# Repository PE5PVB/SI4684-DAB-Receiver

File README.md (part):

# SI4684 FM/DAB Receiver v2.2.1

Advanced FM, RDS/RBDS, DAB/DAB+ and DAB SlideShow receiver for the **Skyworks SI4684**, **ESP32-WROOM-32D** and a **320×240 ILI9341** display.

Firmware v2.2.1 uses separate SPI controllers for the TFT and radio, supports learned IR remote control, FM/DAB presets, multilingual UI, DAB MOT SlideShow, light-sleep standby and an optional serial control/diagnostic interface. It includes a project-local universal **Si468x driver library** that centralizes the tuner command/CTS/error state machine and supports both bounded polling and real **INTB interrupt-driven handling**.

This project is based on the original open-source SI4684/DAB receiver work published by **PE5PVB**.

## Complete ESP32 build image

Every successful `pio run -e esp32dev` also creates
`.pio/build/esp32dev/receiver-complete.bin`, containing the bootloader,
partition table, boot application image and receiver firmware. Flash this
combined file at **0x0**. Its blank padding covers the NVS partition, so
flashing it clears saved settings, presets and station lists. For normal
updates that retain NVS, use `pio run -e esp32dev -t upload` instead.

The same build also generates `.pio/build/esp32dev/flash-addresses.txt` with
the flash addresses and filenames for the combined image and each individual image.
The framework-provided `boot_app0.bin` is copied into the same build directory,
so all listed binary files are available together.
Choose either the combined image or the individual images when flashing.

> [!CAUTION]
> ## GPIO12 / MTDI eFuse requirement — read before using INTB or IR
>
> On the classic ESP32, **GPIO12 is also the MTDI boot-strapping pin**. At reset it normally selects the VDD_SDIO flash voltage:
>
> - GPIO12 LOW or unconnected → **3.3 V**
> - GPIO12 HIGH → **1.8 V**
>
> **ESP32-WROOM-32D uses 3.3 V flash. For this project, program the VDD_SDIO eFuses to a fixed 3.3 V before using GPIO12 as either Si4684 INTB or IR receiver input.** This also applies to `GPIO12 = AUTO` if the INTB line is physically fitted.
>
> An Si4684 INTB output or a demodulated IR receiver normally idles HIGH. Without the eFuse override, a HIGH level present during reset can select 1.8 V for a 3.3 V flash device and the ESP32 may fail to boot.
>
> If GPIO12 is physically unconnected and the radio is used in polling mode, the eFuse change is not required. A hardware design that independently guarantees the correct VDD_SDIO voltage/strap can also solve the problem, but the standard WROOM-32D build in this project should treat the 3.3 V eFuse setting as mandatory for INTB or IR.
>
> **eFuse programming is permanent and cannot be undone. Verify that the ESP32 module really uses 3.3 V flash before burning it. Do not burn 3.3 V on a module that requires 1.8 V flash.**

Official Espressif references:

- [Set Flash Voltage — ESP32 / espefuse](https://docs.espressif.com/projects/esptool/en/latest/esp32/espefuse/set-flash-voltage-cmd.html)
- [Espressif FAQ — using GPIO12 on ESP32-WROOM-32D](https://docs.espressif.com/projects/esp-faq/en/latest/hardware-related/hardware-design.html)

---

## Main features

### DAB / DAB+

- DAB and DAB+ reception with SI4684.
- Uses the **Skyworks proprietary Si4684 DAB application firmware image** loaded into the tuner at runtime (`dab_6_0_9`, firmware 6.0.9 in the current build).
- Manual multiplex selection, automatic seek/scan and memory mode.
- Up to **99 DAB presets**.
- Ensemble and service list handling.
- Service selection from the channel/service list.
- Service ID (SID), Ensemble ID (EID), ECC/country information.
- Programme Type (PTY).
- Dynamic Label / DLS radiotext.
- Bitrate, sample rate, audio mode, service type and protection information when supplied by the tuner.
- DAB time/date information.
- DAB SlideShow / MOT reception.
- Automatic or manual SlideShow display.
- Character conversion for DAB labels/DLS including EBU Latin, UCS-2 and UTF-8 paths used by the firmware.

### FM

- FM reception using the **Skyworks proprietary Si4684 FM/FMHD application firmware image** loaded into the tuner at runtime (`fmhd_5_3_3`, firmware 5.3.3 in the current build).
- FM reception with regional band profiles:
  - **Europe:** 87.5–108.0 MHz, 100 kHz raster, 50 µs de-emphasis, RDS.
  - **North America:** 87.9–107.9 MHz, 200 kHz raster, 75 µs de-emphasis, RBDS.
  - **Japan:** 76.0–95.0 MHz, 100 kHz raster, 50 µs de-emphasis, RDS.
- Manual tuning, automatic seek and memory mode.
- Up to **99 FM presets**.
- RDS/RBDS:
  - PI, region-specific PTY text, PS and RadioText;
  - AF list decoding from group 0A plus optional, default-off automatic AF
    switching with mandatory PI verification and RSSI/SNR hysteresis;
  - TP and TA indicators;
  - validated group 4A Clock-Time/date, shown in System Information and used
    for the displayed local clock after applying the broadcast UTC offset;
  - bounded full-band station scan with PI/PS/RSSI/SNR list records;
  - stabilized PS and RadioText assembly.
- Stereo/mono indication.
- Stereo blend indication.
- Multipath indication.
- RSSI and SNR display.
- Region-aware fine tuning and seek spacing.

### User interface

- 320×240 ILI9341 color TFT.
- Smooth fonts and sprite-based UI.
- Multiple color themes.
- Adjustable backlight.
- Signal units: `dBµV`, `dBf`, `dBm`.
- Service/channel list.
- System Information screen.
- Configurable inactivity time-out.
- Eight UI languages:
  - English
  - Dutch
  - Greek
  - German
  - French
  - Spanish
  - Polish
  - Romanian

### Other functions

- Learned IR remote control on GPIO12.
- IR Learn / Clear / Test menu.
- Light-sleep standby with state retained in RAM.
- Wake by physical STANDBY button.
- Optional wake by the learned IR STANDBY command when `GPIO12 = IR`.
- Direct NVS settings, presets, learned IR profile and persistent FM/DAB scan lists.
- Serial control protocol at 115200 baud.
- Runtime `DEBUG` command for detailed FM/DAB/RDS/SLS/SPI/RAM diagnostics.
- Shared ILI9341/SI4684 reset recovery.
- Dedicated TFT VSPI and radio HSPI buses.

---

# Hardware

## ESP32

The project targets a classic **ESP32-WROOM-32D / ESP32 Dev Module**.

## TFT — ILI9341 / TFT_eSPI

| Signal | ESP32 GPIO |
|---|---:|
| SCLK | 18 |
| MISO | 19 |
| MOSI | 23 |
| CS | 5 |
| DC | 4 |
| RESET | 17, shared with SI4684 RSTB |
| Backlight PWM | 2 |

The TFT uses **VSPI/SPI3**. `TFT_RST=-1` is intentional: GPIO17 is controlled by the application because the TFT reset and Si4684 RSTB share the same physical net.

## SI4684

| Signal | ESP32 GPIO |
|---|---:|
| SCLK | 14 |
| MISO | 16 |
| MOSI | 13 |
| CS | 15 |
| RSTB | 17, shared with TFT RESET |
| INTB | 12 when fitted |

The Si4684 uses a dedicated **HSPI/SPI2** instance. The radio SPI bus is initialized once and is not re-created during normal FM/DAB operation.

Firmware v2.2.1 uses a project-local universal **`Si468x` driver layer** (`vendor/si468x/Si468x.*`). It provides the common low-level transport and command state machine for the tuner. In particular it supports:

- normal bounded **polling** for CTS/status completion;
- **INTB interrupt-driven** command/event handling when the Si4684 INTB line is connected;
- polling as a safety/fallback path even when INTB is enabled;
- common command/reply parsing and device-error reporting;
- the same transport architecture for both FM and DAB firmware images.

`AUTO` first observes GPIO12 during real tuner commands. If no usable INTB
transition is proven, an unconnected GPIO12 remains in non-blocking polling
mode. With INTB connected, interrupt completion is the fast path and a bounded
2 ms safety poll remains enabled; occasional `ctsPoll` completions do not by
themselves indicate fallback or a wiring fault. The ISR only records an event;
all SPI work remains in the foreground transport pump.

Application-level radio work is scheduled cooperatively and starts at most one
new Si4684 command per pass. Continuous DSRV/MOT traffic is drained in bounded
bursts of four commands; overdue RF status and then one phase-separated metadata
command receive a turn before draining resumes. Stable intervals are:

- DAB RF status 1000 ms; signal/Q UI 500 ms;
- DAB audio and current-service metadata 10 s, ensemble 30 s, time and current
  subchannel 60 s;
- FM RSQ 500 ms; ACF 1000 ms; signal/multipath UI 250 ms;
- FM RDS remains IRQ-driven with an 80 ms polling fallback.

DAB service changes use one explicit non-blocking switch state machine. It
serializes data STOP, audio STOP, a 200 ms settle interval, the new audio START,
another 200 ms settle after confirmation, and only then resolves and starts the
matching data component. A rapid A -> B -> C selection supersedes older request
IDs; completion of an already submitted command is reconciled with the physical
tuner state before the newest request continues. Metadata callbacks only request
data-component evaluation, so there is a single authority that can issue data
START and no callback-driven command storm.

Si4684 `NOT_AVAILABLE` (`0x03`) is treated as a responsive command rejection and
uses bounded non-blocking backoff. It does not trigger a cold reset. Only repeated
CTS timeouts use the existing bounded transport recovery. If slideshow data cannot
be started, audio remains playing and SLS is retried later; MOT objects received
outside the confirmed current data-service context are discarded. Data association
prefers a component with the active audio SID and accepts the legacy ensemble-wide
fallback only when exactly one eligible component exists. Ensembles that carry
MOT/SLS directly in the confirmed audio service PAD do not require a separate
type-3 data-service START; that context becomes valid after audio confirmation
and its settle interval.

The signal display has two stages: each new RF sample updates the radio filter
once, while the faster UI timer only interpolates toward that filtered target.
The `DEBUG` command uses throttled MOT milestones. `DEBUG SLSV` (or
`DEBUG VERBOSE`) explicitly toggles per-segment tracing; low-priority segment
lines are dropped and counted when the UART TX buffer is full.

The current build loads Skyworks-provided proprietary application images into the Si4684 with `LOAD_INIT` / `HOST_LOAD` / `BOOT` when changing the active radio firmware:

- DAB: `dab_6_0_9`
- FM/FMHD: `fmhd_5_3_3`

These tuner firmware images are **proprietary Skyworks material**, not GPL application source code. Their use and redistribution are subject to the applicable Skyworks terms/licence.

## Controls

| Control | ESP32 GPIO |
|---|---:|
| Upper rotary A | 27 |
| Upper rotary B | 34 |
| Upper rotary push / OK | 25 |
| Lower rotary A | 33 |
| Lower rotary B | 32 |
| Lower rotary push / Volume | 35 |
| MODE | 39 |
| STANDBY | 36 |
| SLIDESHOW | 26 |

GPIO34–39 are input-only pins and have no internal pull resistors; the PCB must provide the required external bias.

## Other hardware

- TPA6130A2 headphone amplifier over I²C.
- GPIO17 is a shared active-low hardware reset for both ILI9341 and SI4684.
- GPIO12 is mutually exclusive in the hardware design: connect it to **Si4684 INTB**, **IR receiver output**, or leave it unused. **Do not tie INTB and an IR receiver output together.**

---

# Mandatory eFuse setup for GPIO12 INTB / IR

## Why this is necessary

GPIO12 is not an ordinary GPIO during ESP32 reset. It is sampled as **MTDI** before the application starts and normally controls the internal VDD_SDIO regulator voltage.

For a normal ESP32-WROOM-32D:

| GPIO12 at reset | Default VDD_SDIO |
|---|---:|
| LOW / NC | 3.3 V |
| HIGH | 1.8 V |

Both of the project use cases below can place a HIGH level on GPIO12 before firmware gets control:

1. **Si4684 INTB connected to GPIO12** — includes explicit `INTB` mode and `AUTO` mode on hardware with INTB fitted.
2. **Demodulated IR receiver connected to GPIO12** — IR receiver outputs normally idle HIGH.

Therefore the recommended and expected configuration for the WROOM-32D build is to permanently force VDD_SDIO to **3.3 V** by eFuse.

## Short programming guide

Install a recent Espressif `esptool` package and identify the ESP32 serial port. The following example uses `COM5`; replace it with your actual port.

### 1. Read the current eFuse state

```text
espefuse --chip esp32 --port COM5 summary
```

Before programming, a factory device normally reports that flash voltage is determined by GPIO12/MTDI.

### 2. Verify the module

Confirm that the module/flash requires **3.3 V**. This README assumes **ESP32-WROOM-32D**.

### 3. Permanently set VDD_SDIO to 3.3 V

```text
espefuse --chip esp32 --port COM5 set-flash-voltage 3.3V
```

The tool displays an irreversible-operation warning and asks for confirmation. Read the proposed operation before confirming it.

Older esptool installations may use the legacy command form:

```text
espefuse.py --port COM5 set_flash_voltage 3.3V
```

### 4. Verify after programming

```text
espefuse --chip esp32 --port COM5 summary
```

A fixed 3.3 V configuration burns the ESP32 VDD_SDIO-related eFuses so GPIO12 is ignored for flash-voltage selection.

### 5. Verify on the receiver itself

Open **System Information** with a short press of the physical STANDBY button. The `VDD_SDIO` row reports both the boot-latched MTDI state and whether voltage selection comes from the strap or eFuse.

Typical examples:

```text
3.3V MTDI:H/EFUSE
3.3V MTDI:L/EFUSE
```

Both mean VDD_SDIO is forced to 3.3 V by eFuse and GPIO12 can safely be HIGH or LOW during reset on the WROOM-32D build.

```text
3.3V MTDI:L/STRAP
```

means the board booted with the normal strap selecting 3.3 V, but the eFuse override is **not** active.

```text
1.8V MTDI:H/STRAP
```

means GPIO12 was sampled HIGH and selected 1.8 V through the strap. This is **not the intended state for ESP32-WROOM-32D**.

> [!WARNING]
> eFuses are one-time programmable. The firmware never burns or changes them automatically. Changing `Settings -> GPIO12` does **not** program the eFuse.

---

# GPIO12 operating modes

Select the role in **Settings -> GPIO12**. Changing the GPIO12 role is a boot-time change: the setting is stored and the ESP32 restarts automatically when Settings is closed.

### AUTO

- Default/universal radio mode.
- The firmware tests for a real Si4684 INTB connection.
- If INTB is detected, radio IRQ operation is used.
- If INTB is not detected, the firmware falls back to bounded polling.
- AUTO never tries to detect an IR receiver.
- If the INTB wire is physically fitted to GPIO12, the 3.3 V eFuse requirement still applies.

### INTB

- Forces GPIO12 to be used as Si4684 INTB.
- FALLING-edge IRQ is installed before normal tuner commands start.
- CTS safety polling remains available as a fallback.
- Requires the GPIO12 / VDD_SDIO boot issue to be solved; for WROOM-32D this README expects the 3.3 V eFuse setting.

### IR

- GPIO12 belongs exclusively to the IR receiver.
- Si4684 runs in polling mode.
- No Si4684 GPIO12 IRQ handler is attached.
- IR Learn/Test functions become active after the restart into IR mode.
- Requires the GPIO12 / VDD_SDIO boot issue to be solved; for WROOM-32D this README expects the 3.3 V eFuse setting.

---

# Physical controls

The radio has two rotary encoders plus MODE, STANDBY and SLIDESHOW buttons.

## Upper rotary encoder — tuning / menu / OK

### Rotate in the main screen

Behavior depends on the selected tune mode:

| Tune mode | DAB | FM |
|---|---|---|
| **MAN** | previous/next DAB channel block | coarse tuning ±1.0 MHz |
| **AUTO** | previous/next live audio service; at a mux boundary search backward/forward for the next receivable mux | live FM seek down/up |
| **MEM** | previous/next stored preset | previous/next stored preset |

In MEM mode, empty preset positions are skipped during normal recall.

### Rotate in Channel List

Moves the highlighted service/station. The selected row is activated with the upper rotary push/OK.

### Rotate in Settings

Moves through menu rows. After a menu item is opened for editing, rotation changes its value.

### Push / OK

- **Main screen, MAN/AUTO:** opens Channel List.
- **Channel List:** starts/confirms the highlighted service/station and returns to the main screen. If the global list is empty, it shows whether a scan has never run or completed without finding a station; OK starts the appropriate full scan.
- **MEM mode:** first press arms preset storage; second press stores the currently tuned station/service in the selected memory position.
- **Settings:** opens the highlighted setting; pressing again closes the edit popup/sub-item.
- **Slideshow/System Info:** returns to the main display where applicable.

### Long push — at least 1 second

- **FM main screen:** performs a non-blocking full-band scan and rebuilds the persistent FM station list. The scan overlay includes a compact band-progress bar. Releasing the encoder does not also perform the short-push action.
- **DAB main screen:** performs a non-blocking scan of all 38 Band-III channels, shows exact channel progress, stores up to 64 audio services in the persistent global list, then restores the previously playing service. DAB AUTO remains a live RF search and does not depend on this database.

## Lower rotary encoder — service / fine tune / volume

### Rotate without volume overlay

- **DAB:** previous/next station from the persistent global scan list. If no
  global list exists, falls back to audio services in the current multiplex.
- **FM AUTO:** previous/next station from the persistent FM scan list. Rotary 2
  has no tuning action when that list is empty.
- **FM MAN/MEM:** previous/next channel using the selected region raster:
  - Europe/Japan: 100 kHz
  - North America: 200 kHz
- No hidden tuning action is performed while System Information is open.

### Push

Opens the volume overlay.

### Rotate while volume overlay is open

Changes headphone volume. The overlay closes automatically after inactivity or can be closed by pressing the lower encoder again.

## MODE button

### Short press

- Main screen: cycles **MAN -> AUTO -> MEM -> MAN**.
- Full-screen sub-view: returns to the main screen.
- Settings: closes Settings and commits actual changed values.

### Long press — more than 1 second

- Main screen: opens **Settings**.

## STANDBY button

### Short press

Toggles **System Information**.

### Long press — more than 1 second

Enters light-sleep standby.

### While preset storage is armed

If MEM storage has been armed with the upper rotary push, pressing STANDBY deletes/clears the selected preset instead of opening System Information or entering standby.

## SLIDESHOW button

DAB only:

- If a complete SlideShow image is available, opens it immediately.
- If a MOT object is currently being received, opens a waiting/progress view and displays the image when reception completes.
- Press again to leave SlideShow.
- No action in FM mode.

---

# Tune modes and presets

## MAN

Direct manual tuning.

- DAB upper rotary: steps through DAB channel blocks.
- FM upper rotary: ±1.0 MHz coarse step.
- FM lower rotary: exact regional channel raster.

## AUTO

AUTO always searches current RF reception; it never treats an old scan list as
the authoritative tuning source.

- **FM:** every rotary action starts the Si4684 live seek in that direction.
- **DAB:** first selects the adjacent valid audio service in the current live
  multiplex. At the first/last service boundary it scans the fixed Band-III
  channel table in the requested direction, waits for a current service list
  and service-mode classification, then starts the last/first audio service.
  The 38-channel table wraps in both directions.
- A short upper-rotary push opens the separately scanned global FM/DAB list.
  FM stations without stable PS are shown by frequency. The DAB Channel List
  never substitutes the current-multiplex service table for the global scan
  database; current-multiplex services remain selectable with the lower rotary.
  An empty list explicitly reports either `SCAN NOT RUN` or `NO STATIONS FOUND`
  and offers a full scan with OK.
- Rotary 2 uses these global scan lists directly on the main screen. DAB falls
  back to the current multiplex only when its global list is unavailable; FM
  AUTO deliberately does nothing when its global list is unavailable. A DAB
  global-list detent also closes a manually armed `Loading slideshow` view and
  continues directly with the adjacent station.

- Repeating/holding IR TUNE does not continually restart an already running AUTO seek.

## MEM

Recall/store mode for 99 presets.

### Recall

Rotate the upper encoder. Empty positions are skipped and the stored DAB service or FM frequency is tuned.

### Store

1. Select `MEM` mode.
2. Press the upper rotary once to arm preset storage.
3. Rotate to the desired memory position if needed.
4. Press the upper rotary again to save the current service/station.

FM presets store frequency, PI and PS label when available. DAB presets store channel, service ID and service label.

### Delete

1. Select/arm the preset position as above.
2. Press STANDBY while preset storage is armed.
3. The selected preset is cleared.

---

# IR remote control

IR support is available only when **Settings -> GPIO12 -> IR** is selected and the radio has restarted.

A demodulated IR receiver output is connected to GPIO12. GPIO12 is then owned by the IR decoder and the Si4684 runs in polling mode.

> [!CAUTION]
> An IR receiver normally idles HIGH. On ESP32-WROOM-32D, program VDD_SDIO to fixed 3.3 V by eFuse before using the IR input on GPIO12. See the mandatory eFuse section above.

The runtime receiver uses a project-local GPIO edge-capture and state-machine implementation, so the full Arduino-IRremote library is not required as a build dependency. However, the supported protocol IDs, timing constants and decoder behaviour in `ir_decode.cpp` are **derived from the public Arduino-IRremote 4.7.1 decoder sources**. Those derived portions are used under the **MIT License** and retain the corresponding copyright/licence notice in the source file.

## Learning a remote

Open:

**Settings -> IR Remote -> Learn**

The wizard learns these eight actions in order:

1. `TUNE +`
2. `TUNE -`
3. `OK`
4. `VOL +`
5. `VOL -`
6. `MODE`
7. `SLIDESHOW`
8. `STANDBY`

Learning behavior:

- The previous profile remains active until all eight new keys are learned successfully.
- Repeat frames are ignored while learning.
- Each key must be released before the next step.
- Duplicate assignments are rejected.
- The completed profile is written only when it differs from the stored profile.

## IR Remote menu

### Learn

Starts the eight-key learning wizard.

### Clear

Deletes the learned profile after confirmation.

### Test

Shows decoded protocol/address/command and the mapped action without executing the radio action.

## IR actions during normal operation

| Learned key | Short press | Hold / long press | Repeat behavior |
|---|---|---|---|
| **TUNE +** | DAB: normal up action; FM MAN: one regional raster step up; AUTO/MEM: normal up action | repeats after hold delay except AUTO seek | auto-repeat after about 500 ms; AUTO repeats are ignored so an active seek is not restarted |
| **TUNE -** | DAB: normal down action; FM MAN: one regional raster step down; AUTO/MEM: normal down action | repeats after hold delay except AUTO seek | auto-repeat after about 500 ms; AUTO repeats are ignored so an active seek is not restarted |
| **OK** | same as upper rotary push | no separate long action | repeats ignored |
| **VOL +** | volume +2 | continues increasing | auto-repeat after about 500 ms |
| **VOL -** | volume -2 | continues decreasing | auto-repeat after about 500 ms |
| **MODE** | cycle MAN/AUTO/MEM after key release | **hold >= 1 s: switch DAB <-> FM once** | handled as one short-or-long action, not repeated |
| **SLIDESHOW** | toggle DAB SlideShow | no separate long action | repeats ignored |
| **STANDBY** | enter standby; **when waking from light sleep use a double-click (two presses)** | no separate long action | repeats ignored during normal operation; wake qualification uses the second complete learned STANDBY frame |

### IR TUNE +/- behavior

IR TUNE follows the radio context, with one deliberate FM difference from the physical upper encoder: in **FM MAN** it uses the selected region's exact channel raster (100 kHz Europe/Japan, 200 kHz North America), so every valid station remains reachable from a remote that has only one TUNE +/- pair. In AUTO mode the first press starts seek and held-key repeats are ignored until a new press.

### IR MODE short press

A short learned MODE press is deliberately executed **on release**. It performs the same normal mode action as the physical MODE short press: MAN/AUTO/MEM cycling or contextual return behavior.

### IR MODE long press

Hold the learned MODE key continuously for at least **1 second**:

```text
DAB <-> FM
```

The long action is fired only once. Releasing the key does not then generate the short MODE action.

## IR WAKE — double-click is required

When waking the receiver from light sleep with the learned IR **STANDBY** key, use a **double-click: press STANDBY twice in quick succession**. This is the documented and required IR wake gesture for this firmware.

Why two presses are used:

1. **First STANDBY press** — generates the GPIO12 edge that wakes the ESP32 from light sleep. Because the CPU starts in the middle of that transmission, the beginning of the IR frame may be missing and it is not accepted as the wake command.
2. **Second STANDBY press** — must arrive within the wake qualification window (up to about **1.5 seconds**) and supplies a complete learned STANDBY frame. Only after this frame is decoded and matched does the firmware restore the display/audio and complete wake-up.

So the expected user action is:

```text
IR STANDBY:  press -> press   (double-click)
```

This is intentionally **not** a general double-click function for other IR keys during normal operation. It is specific to IR wake from light sleep and prevents random IR traffic, noise, or another learned button from turning the receiver on.

The physical STANDBY button on GPIO36 wakes the receiver immediately and does **not** require a double-click.

---

# Settings

Open Settings with a **long physical MODE press (>1 s)**.

Use the upper rotary to navigate, press the upper rotary to edit/select, rotate to change values, and press again to leave the edit item. Press MODE to leave Settings.

The menu contains:

1. **Language**
2. **Brightness**
3. **Theme**
4. **Auto slideshow**
5. **Signal unit** — dBµV / dBf / dBm
6. **Time-out Timer** — Off / 15 / 30 / 60 / 90 minutes
7. **Radio mode** — DAB / FM
8. **FM Region** — Europe / North America / Japan
9. **GPIO12** — AUTO / INTB / IR
10. **IR Remote** — Learn / Clear / Test
11. **FM Seek** — Weak / Normal / Strong acceptance thresholds
12. **About**

Settings are edited in RAM and committed when leaving Settings. Values that did not actually change are not unnecessarily rewritten to NVS.

Changing GPIO12 causes an automatic restart after the settings have been committed, because GPIO12 ownership is established during boot.

---

# Boot-time button shortcuts

The following physical keys are sampled during power-up:

| Keys held during boot | Function |
|---|---|
| **SLIDESHOW only** | invert rotary direction and save it |
| **MODE** | rotate/flip the display orientation by 180° and save it |
| **SLIDESHOW + upper rotary push/OK** | factory defaults / clear settings and presets, then restart |

Release the key(s) when the on-screen instruction asks for it.

---

# System Information

Open with a short physical STANDBY press.

The page includes:

- Si4684 tuner type and firmware version.
- Active radio mode.
- Radio control mode: INTB / polling / detection state.
- GPIO12 configured/runtime role and live electrical level.
- VDD_SDIO status including boot-latched MTDI and STRAP/EFUSE source.
- ESP32 revision, CPU frequency and firmware version.
- Uptime.
- Reset reason.
- Free/minimum heap.
- Largest heap block and calculated fragmentation.

The VDD_SDIO row is especially useful after the GPIO12 eFuse programming described above.

---

# DAB SlideShow / MOT

The firmware implements a RAM-only DAB MOT SlideShow path intended for the DAB SlideShow Simple Profile used by this receiver.

- Maximum MOT image payload buffer: **51,200 bytes (50 KiB)**.
- Supported display size: up to **320×240**.
- JPEG artwork larger than the panel but fitting after the profile's exact
  50% reduction is centred at half size; a 320×320 slide is shown as 160×160.
- Static PNG support.
- Single-scan baseline JPEG: grayscale or three-component YCbCr, including
  4:4:4, 4:2:2 and 4:2:0 sampling and valid DRI/RST restart sequences.
- Progressive SOF2 Huffman JPEG: grayscale or three-component YCbCr 4:4:4,
  4:2:2 and 4:2:0, including spectral-selection/refinement scans, EOB runs and
  valid DRI/RST sequences. It is decoded by replaying scans for one MCU row at
  a time, without allocating a full-frame coefficient buffer.
- Baseline multi-scan, arithmetic-coded JPEG, four-component CMYK/YCCK JPEG
  and images above 320×240 remain unsupported. They are rejected before
  `fadeDown()` or `fillScreen()` and the existing UI remains visible.
- JPEG entropy data and PNG decode are checked in a dry validation pass before
  the render pass. `render=OK` is emitted only after every expected MCU row or
  PNG line has decoded successfully.
- If a manually armed slide is rejected, the temporary "Loading slideshow"
  overlay is explicitly closed and the normal radio screen remains usable.
- Shared early decoder workspace: **76,800 bytes**.
- No late JPEG/PNG fallback `malloc/calloc` allocation during normal rendering.
- Incoming MOT segments may arrive out of order; the collector tracks received segments and assembles only a complete object.
- A partial old Transport ID is abandoned when a new object begins.

### Manual SlideShow

Press SLIDESHOW or the learned IR SLIDESHOW key.

### Automatic SlideShow

Enable **Settings -> Auto slideshow**. A completed image can automatically enter the SlideShow view.

---

# Standby / light sleep

A long physical STANDBY press, or the learned IR STANDBY action, enters ESP32 light sleep.

During light sleep:

- CPU execution pauses.
- RAM is retained.
- Si4684 firmware/service state remains resident.
- MOT/decoder workspaces remain allocated.
- ILI9341 enters Sleep In.
- Backlight is off.
- TPA6130A2 is shut down.
- GPIO17 shared reset is held HIGH.
- VDD_SDIO is explicitly kept powered so GPIO16/17 state is retained correctly.

Wake sources:

- Physical STANDBY GPIO36 LOW — always available and wakes immediately.
- GPIO12 IR wake — available only when `GPIO12 = IR` **and** a learned IR profile exists. **IR wake requires a double-click of the learned STANDBY key:** the first press wakes the ESP32, the second complete frame within about 1.5 s confirms the learned STANDBY command.
- GPIO12 is not used as a sleep wake source in AUTO or INTB mode.

After wake, the TFT uses the ILI9341 wake sequence rather than an unnecessary software reset, then the main UI is redrawn before the backlight is restored.

---

# Serial interface and DEBUG diagnostics

UART speed:

```text
115200 baud
```

Normal application diagnostics are intentionally **OFF** so the UART is not continuously flooded by FM/DAB polling, RDS and MOT progress messages.

Send the bare command:

```text
DEBUG
```

The receiver replies:

```text
[DEBUG] diagnostics ON
```

Detailed diagnostics then become available, including:

- boot/RAM information;
- FM status;
- DAB status;
- RDS PI/PTY/PS/RT plus AF, TP/TA and validated CT processing;
- FM full-scan discoveries/completion and DAB AUTO transitions;
- MOT headers and segment progress;
- SlideShow JPEG/PNG status;
- SI4684 SPI replies and errors;
- firmware HOST_LOAD progress;
- IR frames and sleep/wake qualification;
- memory-integrity reports.

Send `DEBUG` again to disable them:

```text
[DEBUG] diagnostics OFF
```

The command parser accepts CR, LF, CRLF and also a command sent with no line ending after a short idle timeout.

Critical startup/fatal errors remain visible even when DEBUG is off.

The external serial control protocol remains independent of the diagnostic gate. Main control commands include `ENABLE`, `TUNE`, `SERVICE` and `INTERVAL`; see `Serial_protocol.pdf` / `Serial_protocol.docx` in the repository for the complete protocol description.

---

# NVS and stored data

Runtime data is stored directly in the `si4684` NVS namespace. The stable keys
are `settings`, `dab_presets`, `fm_presets`, `ir_profile`, `fm_scan`,
`fm_scan_reg`, `fm_scan_done`, `dab_scan` and `dab_scan_done`; no NVS
schema/version field is used. Missing records, unexpected record lengths and
out-of-range setting values are replaced by safe defaults.

Stored information includes:

- UI/settings values.
- Current DAB/FM mode.
- DAB restore frequency/service ID.
- FM frequency/region.
- 99 DAB presets.
- 99 FM presets.
- GPIO12 role.
- Learned eight-key IR profile.
- Completed FM station scan (up to 64 PI/frequency records with PS and quality).
- Completed DAB Band-III scan (up to 64 audio-service records).

Legacy EEPROM-emulation data is not read or migrated, and the EEPROM library is
not linked. Runtime writes use compact direct-NVS records. Settings/preset
writes remain delayed or grouped, and station lists are written only after a
completed scan. Erased, missing, partial or malformed NVS records are replaced
with safe defaults.

---

# SPI and reset architecture

The ESP32 uses two independent SPI hosts:

```text
ILI9341  -> VSPI / SPI3
SI4684   -> HSPI / SPI2
```

This prevents both devices from trying to initialize/own the same SPI host.

GPIO17 is physically shared by TFT RESET and Si4684 RSTB. The application therefore follows these rules:

- `TFT_RST=-1` in TFT_eSPI.
- GPIO17 is driven manually.
- Cold boot performs one controlled shared hardware reset.
- Normal light-sleep wake does not reset the tuner or reinitialize the SPI hosts.
- FM/DAB firmware-image changes use the controlled shared-reset recovery path while the backlight is hidden.

---

# Memory strategy

Large lifetime buffers are allocated early from internal RAM, before TFT sprites/fonts can fragment the heap:

- DAB MOT buffer: 51,200 bytes.
- JPEG/PNG shared decoder workspace: 76,800 bytes.
- Si4684 HOST_LOAD workspace: 4,096 bytes.

These blocks remain allocated for the firmware lifetime. Small fixed runtime state such as FM preset cache and IR learned/work tables is kept in fixed storage. Runtime rendering avoids large fallback heap allocations.

System Information and DEBUG diagnostics can be used to watch free heap, minimum heap and largest allocatable block.

---

# Building with PlatformIO

The current `platformio.ini` is the authoritative build configuration.

```text
pio run -e esp32dev
```

Important build settings include:

- platform: `espressif32@6.9.0` (Arduino-ESP32 2.x toolchain)
- board: `esp32dev`
- framework: Arduino
- monitor: 115200 baud
- custom `partitions.csv`
- `CORE_DEBUG_LEVEL=1`
- ILI9341/TFT_eSPI pin setup passed through build flags
- TFT SPI frequency: 27 MHz
- `TFT_RST=-1`
- smooth fonts enabled

Current library dependencies declared by PlatformIO:

- `paulstoffregen/Time`
- `bodmer/TFT_eSPI`
- `bitbank2/PNGdec`

The IR receiver/capture runtime is implemented locally and therefore does not require Arduino-IRremote as a PlatformIO dependency. The protocol decoders/timing behaviour in `ir_decode.cpp` are derived from **Arduino-IRremote 4.7.1** and used under its MIT licence terms.

---

# Software architecture, firmware and acknowledgements

## Universal Si468x driver

Firmware v2.2.1 uses the universal **Si468x** library/driver layer. The same driver handles low-level Si468x command transport for both FM and DAB operation and supports two radio-control methods:

- **POLL** — bounded CTS/status polling;
- **INTB** — hardware interrupt/event handling on GPIO12, with polling retained as a safety fallback.

`AUTO` mode can detect a usable INTB connection and select interrupt handling automatically; otherwise the driver continues in polling mode. This makes the radio code usable on boards both with and without the INTB connection.

## Skyworks Si4684 firmware images

The ESP32 application does not implement the DAB or FM demodulator internally. The Si4684 requires its vendor application firmware to be uploaded after reset. The current project contains/uses the Skyworks application images required by the tuner:

- **DAB 6.0.9** (`dab_6_0_9`)
- **FM/FMHD 5.3.3** (`fmhd_5_3_3`)

They are transferred to the Si4684 using the tuner `LOAD_INIT`, `HOST_LOAD` and `BOOT` sequence. These images are **proprietary Skyworks firmware**, are not made open-source by this project, and are not covered by the GPL licence that applies to the receiver application source. Users/distributors are responsible for complying with the applicable Skyworks terms.

## IR decoder origin

The IR subsystem uses its own ESP32 GPIO edge capture, timing collection, learning, wake qualification and runtime action state machines. For protocol decoding, `ir_decode.cpp` uses protocol definitions, timings and decoder behaviour derived from the public **Arduino-IRremote 4.7.1** sources. The relevant derived code is used under the **MIT License**, with attribution/licence text retained in the source. This gives the project broad remote-protocol compatibility without requiring the complete Arduino-IRremote runtime/library dependency.

## Original open-source project

This receiver is **based on the original open-source SI4684/DAB receiver project by PE5PVB**, which provided the foundation for the hardware and software concept.

Original project information and build material remain linked in the resources section below.

---

# First-time setup checklist

1. Assemble the board and verify all supply voltages.
2. Confirm the ESP32 module type and flash voltage.
3. **If GPIO12 will be connected to Si4684 INTB or an IR receiver, burn the ESP32-WROOM-32D VDD_SDIO eFuse to fixed 3.3 V before normal use.**
4. Verify the burn with `espefuse ... summary`.
5. Build and flash firmware v2.2.1.
6. Start with `GPIO12 = AUTO` if no IR receiver is fitted.
7. For a known INTB-wired board, select `GPIO12 = INTB` if desired.
8. For IR hardware, select `GPIO12 = IR`, leave Settings and allow the automatic restart.
9. Open `Settings -> IR Remote -> Learn` and learn all eight keys.
10. For IR standby wake, remember that **WAKE uses a double-click of the learned STANDBY key**: first press wakes the CPU, second press confirms the full learned frame.
11. Check System Information, especially `GPIO12` and `VDD_SDIO`.
12. Send `DEBUG` over UART only when detailed diagnostics are needed.

---

# Troubleshooting

## ESP32 does not boot after connecting INTB or IR to GPIO12

Disconnect the GPIO12 peripheral and check whether the board boots again. If it does, verify the VDD_SDIO/eFuse configuration. On WROOM-32D a HIGH GPIO12 strap can select 1.8 V unless the flash voltage has been forced to 3.3 V.

## System Information shows `.../STRAP`

The VDD_SDIO voltage is still being selected by the boot strap. For the WROOM-32D build with INTB or IR on GPIO12, program and verify the fixed 3.3 V eFuse setting.

## IR menu Learn/Test is inactive

Select `Settings -> GPIO12 -> IR`, exit Settings, and allow the automatic restart. IR capture is initialized only after booting in explicit IR mode.

## IR does not wake the radio

- A valid learned profile must exist.
- GPIO12 must be configured as IR.
- The IR receiver must return to idle HIGH before sleep is armed.
- **Use a double-click of the learned STANDBY key.** The first press wakes the ESP32; the second complete learned frame must arrive within about 1.5 s to confirm wake.

## Serial monitor is quiet

This is normal. Send:

```text
DEBUG
```

to enable diagnostics.

## SlideShow is not displayed

A complete MOT object must be received. With DEBUG enabled, inspect SLS/MOT
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
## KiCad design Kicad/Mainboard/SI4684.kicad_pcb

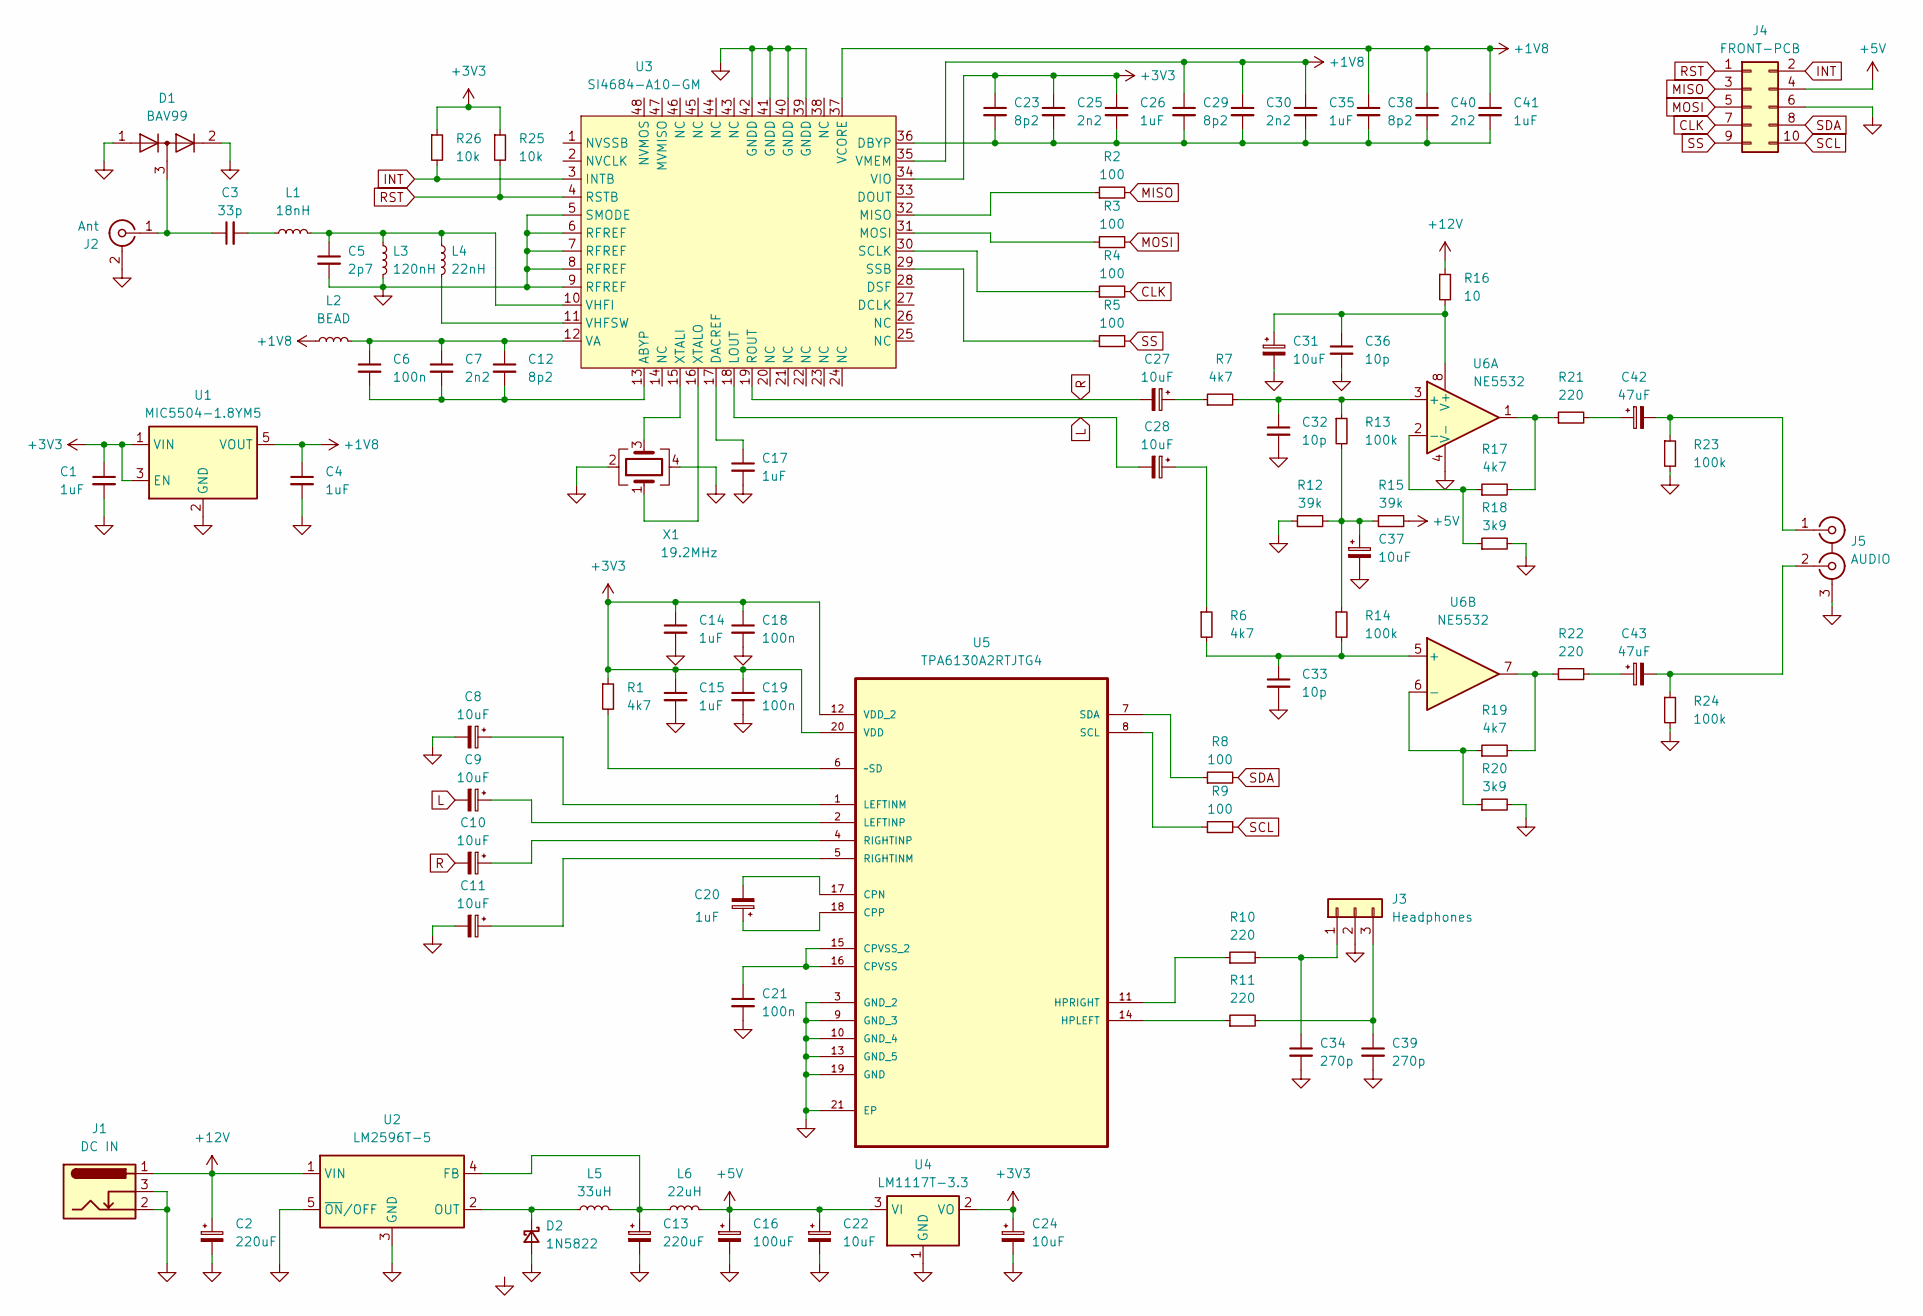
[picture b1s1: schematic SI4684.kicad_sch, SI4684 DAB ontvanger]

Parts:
C1, C4, C14, C15, C17, C26, C35, C41: 1uF; C_0603_1608Metric
C2, C13: 220uF; CP_Radial_D10.0mm_P3.50mm
C3: 33p; C_0603_1608Metric
C5: 2p7; C_0603_1608Metric
C6, C18, C19, C21: 100n; C_0603_1608Metric
C7, C25, C30, C40: 2n2; C_0603_1608Metric
C8, C9, C10, C11, C22, C24, C27, C28, C31, C37: 10uF; CP_Radial_D5.0mm_P2.00mm
C12, C23, C29, C38: 8p2; C_0603_1608Metric
C16: 100uF; CP_Radial_D10.0mm_P3.50mm
C20: 1uF; CP_Radial_D5.0mm_P2.00mm
C32, C33, C36: 10p; C_Disc_D3.0mm_W2.0mm_P2.50mm
C34, C39: 270p; C_0603_1608Metric
C42, C43: 47uF; CP_Radial_D5.0mm_P2.00mm
D1: BAV99; SOT-23
D2: 1N5822; D_DO-201_P12.70mm_Horizontal
J1: DC IN; BarrelJack_Horizontal
J2: Ant; SMA_Amphenol_132134-16_Vertical
J3: Headphones; JST_PH_B3B-PH-K_1x03_P2.00mm_Vertical
J4: FRONT-PCB; IDC-Header_2x05_P2.54mm_Vertical
J5: AUDIO; FC68405_cinch
L1: 18nH; L_0603_1608Metric
L2: BEAD; L_0603_1608Metric
L3: 120nH; L_0603_1608Metric
L4: 22nH; L_0603_1608Metric
L5: 33uH; L_Radial_D7.2mm_P3.00mm_Murata_1700
L6: 22uH; L_Radial_D7.2mm_P3.00mm_Murata_1700
R1: 4k7; R_0603_1608Metric
R2, R3, R4, R5, R8, R9: 100; R_0603_1608Metric
R6, R7, R17, R19: 4k7; R_Axial_DIN0207_L6.3mm_D2.5mm_P10.16mm_Horizontal
R10, R11: 220; R_0603_1608Metric
R12, R15: 39k; R_Axial_DIN0207_L6.3mm_D2.5mm_P10.16mm_Horizontal
R13, R14, R23, R24: 100k; R_Axial_DIN0207_L6.3mm_D2.5mm_P10.16mm_Horizontal
R16: 10; R_Axial_DIN0207_L6.3mm_D2.5mm_P10.16mm_Horizontal
R18, R20: 3k9; R_Axial_DIN0207_L6.3mm_D2.5mm_P10.16mm_Horizontal
R21, R22: 220; R_Axial_DIN0207_L6.3mm_D2.5mm_P10.16mm_Horizontal
R25, R26: 10k; R_0603_1608Metric
U1: MIC5504-1.8YM5; SOT-23-5
U2: LM2596T-5; TO-220-5_Vertical
U3: SI4684-A10-GM; QFN-48-1EP_7x7mm_P0.5mm_EP5.3x5.3mm
U4: LM1117T-3.3; TO-220-3_Vertical
U5: TPA6130A2RTJTG4; QFN-20-1EP_4x4mm_P0.5mm_EP2.7x2.7mm; MPN TPA6130A2RTJTG4
U6: NE5532; DIP-8_W7.62mm_LongPads
X1: 19.2MHz; Crystal_SMD_3225-4Pin_3.2x2.5mm

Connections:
+1V8: C4.1, C29.1, C30.1, C35.1, C38.1, C40.1, C41.1, L2.1, U1.5 (VOUT), U3.35 (VMEM), U3.37 (VCORE)
+3V3: C1.1, C14.1, C15.1, C18.1, C19.1, C23.1, C24.1, C25.1, C26.1, R1.1, R25.1, R26.1, U1.1 (VIN), U1.3 (EN), U3.34 (VIO), U4.2 (VO), U5.12 (VDD_2), U5.20 (VDD)
+5V: C16.1, C22.1, J4.4, L6.2, R15.2, U4.3 (VI)
+12V: C2.1, J1.1, R16.1, U2.1 (VIN)
CLK: J4.7, R4.2
GND: C1.2, C2.2, C4.2, C5.2, C8.2, C11.2, C13.2, C14.2, C15.2, C16.2, C17.2, C18.2, C19.2, C21.2, C22.2, C24.2, C31.2, C32.2, C33.2, C34.2, C36.2, C37.2, C39.2, D1.1 (K), D1.2 (A), D2.2 (A), J1.2, J1.3, J2.2 (Ext), J3.2, J4.6, J5.3 (EXT), L3.2, R12.1, R18.2, R20.2, R23.2, R24.2, U1.2 (GND), U2.3 (GND), U2.5 (~ON/OFF), U3.5 (SMODE), U3.6 (RFREF), U3.7 (RFREF), U3.8 (RFREF), U3.9 (RFREF), U3.39 (GNDD), U3.40 (GNDD), U3.41 (GNDD), U3.42 (GNDD), U3.49 (GND), U4.1 (GND), U5.3 (GND_2), U5.9 (GND_3), U5.10 (GND_4), U5.13 (GND_5), U5.19 (GND), U5.21 (EP), U6.4 (V-), X1.2, X1.4
INT: J4.2, R26.2, U3.3 (INTB)
L: C9.2, C28.2, U3.18 (LOUT)
MISO: J4.3, R2.2
MOSI: J4.5, R3.2
unnamed: C3.2, L1.1
unnamed: C27.1, R7.1
unnamed: C28.1, R6.1
unnamed: C37.1, R12.2, R13.2, R14.1, R15.1
unnamed: C42.1, R21.2
unnamed: C43.1, R22.2
unnamed: D2.1 (K), L5.1, U2.2 (OUT)
unnamed: C3.1, D1.3 (K), J2.1 (In)
unnamed: C34.1, J3.1, R10.2
unnamed: C39.1, J3.3, R11.2
unnamed: C42.2, J5.1 (IN1), R23.1
unnamed: C43.2, J5.2 (IN2), R24.1
unnamed: R17.2, R21.1, U6.1
unnamed: R19.2, R22.1, U6.7
unnamed: C13.1, L5.2, L6.1, U2.4 (FB)
unnamed: C6.2, C7.2, C12.2, U3.13 (ABYP)
unnamed: C17.1, U3.17 (DACREF)
unnamed: C23.2, C25.2, C26.2, C29.2, C30.2, C35.2, C38.2, C40.2, C41.2, U3.36 (DBYP)
unnamed: R2.1, U3.32 (MISO)
unnamed: R3.1, U3.31 (MOSI)
unnamed: R4.1, U3.30 (SCLK)
unnamed: R5.1, U3.29 (SSB)
unnamed: C6.1, C7.1, C12.1, L2.2, U3.12 (VA)
unnamed: C5.1, L1.2, L3.1, L4.1, U3.10 (VHFI)
unnamed: L4.2, U3.11 (VHFSW)
unnamed: U3.15 (XTALI), X1.3
unnamed: U3.16 (XTALO), X1.1
unnamed: C20.2, U5.17 (CPN)
unnamed: C20.1, U5.18 (CPP)
unnamed: C21.1, U5.15 (CPVSS_2), U5.16 (CPVSS)
unnamed: R11.1, U5.14 (HPLEFT)
unnamed: R10.1, U5.11 (HPRIGHT)
unnamed: C8.1, U5.1 (LEFTINM)
unnamed: C9.1, U5.2 (LEFTINP)
unnamed: C11.1, U5.5 (RIGHTINM)
unnamed: C10.1, U5.4 (RIGHTINP)
unnamed: R9.1, U5.8 (SCL)
unnamed: R8.1, U5.7 (SDA)
unnamed: R1.2, U5.6 (~SD)
unnamed: C32.1, R7.2, R13.1, U6.3 (+)
unnamed: R17.1, R18.1, U6.2 (-)
unnamed: C33.1, R6.2, R14.2, U6.5 (+)
unnamed: R19.1, R20.1, U6.6 (-)
unnamed: C31.1, C36.1, R16.2, U6.8 (V+)
R: C10.2, C27.2, U3.19 (ROUT)
RST: J4.1, R25.2, U3.4 (RSTB)
SCL: J4.10, R9.2
SDA: J4.8, R8.2
SS: J4.9, R5.2

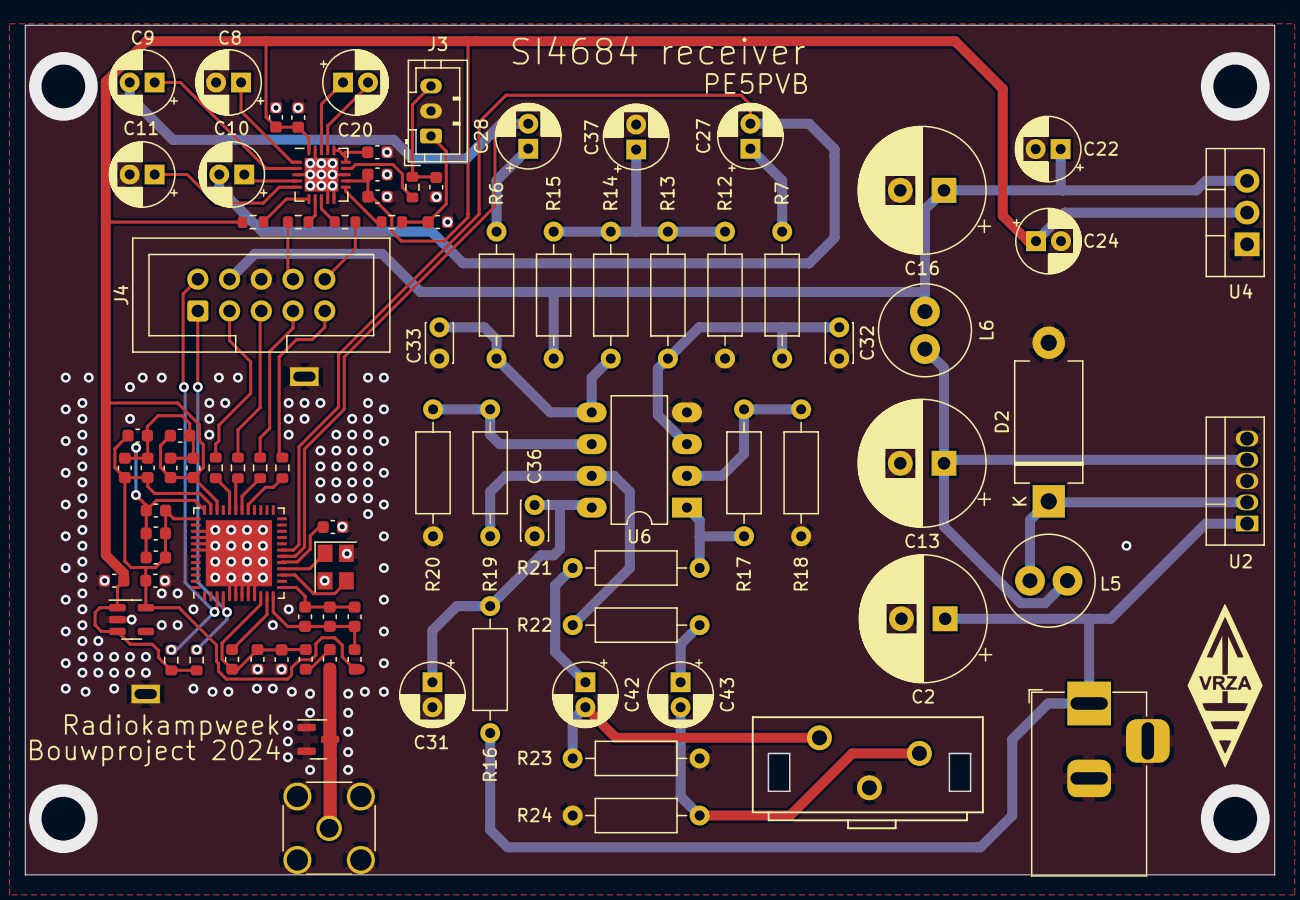
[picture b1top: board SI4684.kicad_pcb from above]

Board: 2 copper layers, 100.0 x 68.0 mm, 89 parts (0 on the bottom side), 59 nets.

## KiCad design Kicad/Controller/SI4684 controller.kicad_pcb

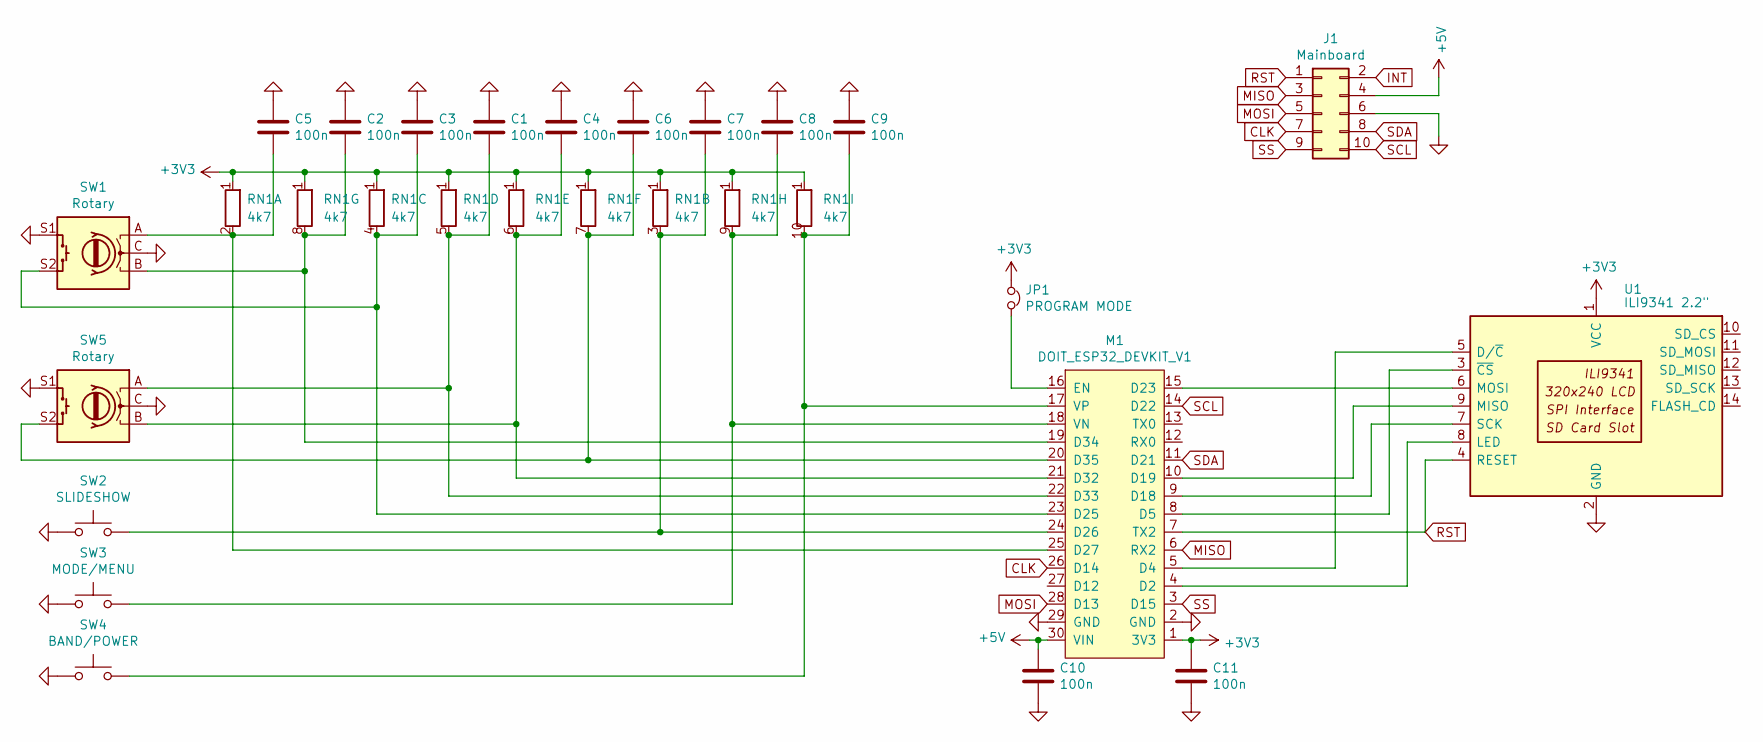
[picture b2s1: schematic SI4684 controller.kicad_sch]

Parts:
C1, C2, C3, C4, C5, C6, C7, C8, C9, C10, C11: 100n; C_Disc_D3.0mm_W2.0mm_P2.50mm
J1: Mainboard; IDC-Header_2x05_P2.54mm_Vertical
JP1: PROGRAM MODE; TestPoint_2Pads_Pitch2.54mm_Drill0.8mm
M1: DOIT_ESP32_DEVKIT_V1; ESP32_DOIT_DEVKIT_V1
RN1: 4k7; R_Array_SIP10
SW1, SW5: Rotary; RotaryEncoder_Alps_EC11E-Switch_Vertical_H20mm
SW2: SLIDESHOW; SW_PUSH_6mm_H7.3mm
SW3: MODE/MENU; SW_PUSH_6mm_H7.3mm
SW4: BAND/POWER; SW_PUSH_6mm_H7.3mm
U1: ILI9341 2.2"; CR2013-MI2120

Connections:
+3V3: C11.1, JP1.1, M1.1 (3V3), RN1.1 (R1), U1.1 (VCC)
+5V: C10.1, J1.4, M1.30 (VIN)
CLK: J1.7, M1.26 (D14)
GND: C1.1, C2.1, C3.1, C4.1, C5.1, C6.1, C7.1, C8.1, C9.1, C10.2, C11.2, J1.6, M1.2 (GND), M1.29 (GND), SW1.C, SW1.S1, SW2.1, SW3.1, SW4.1, SW5.C, SW5.S1, U1.2 (GND)
INT: J1.2
MISO: J1.3, M1.6 (RX2)
MOSI: J1.5, M1.28 (D13)
unnamed: M1.4 (D2), U1.8 (LED)
unnamed: M1.5 (D4), U1.5 (D/~C)
unnamed: M1.8 (D5), U1.3 (~CS)
unnamed: M1.9 (D18), U1.7 (SCK)
unnamed: M1.10 (D19), U1.9 (MISO)
unnamed: M1.15 (D23), U1.6 (MOSI)
unnamed: C3.2, M1.23 (D25), RN1.4 (R3.2), SW1.S2
unnamed: C7.2, M1.24 (D26), RN1.3 (R2.2), SW2.2
unnamed: C5.2, M1.25 (D27), RN1.2 (R1.2), SW1.A
unnamed: C4.2, M1.21 (D32), RN1.6 (R5.2), SW5.B
unnamed: C1.2, M1.22 (D33), RN1.5 (R4.2), SW5.A
unnamed: C2.2, M1.19 (D34), RN1.8 (R7.2), SW1.B
unnamed: C6.2, M1.20 (D35), RN1.7 (R6.2), SW5.S2
unnamed: JP1.2, M1.16 (EN)
unnamed: C8.2, M1.18 (VN), RN1.9 (R8.2), SW3.2
unnamed: C9.2, M1.17 (VP), RN1.10 (R9.2), SW4.2
RST: J1.1, M1.7 (TX2), U1.4 (RESET)
SCL: J1.10, M1.14 (D22)
SDA: J1.8, M1.11 (D21)
SS: J1.9, M1.3 (D15)

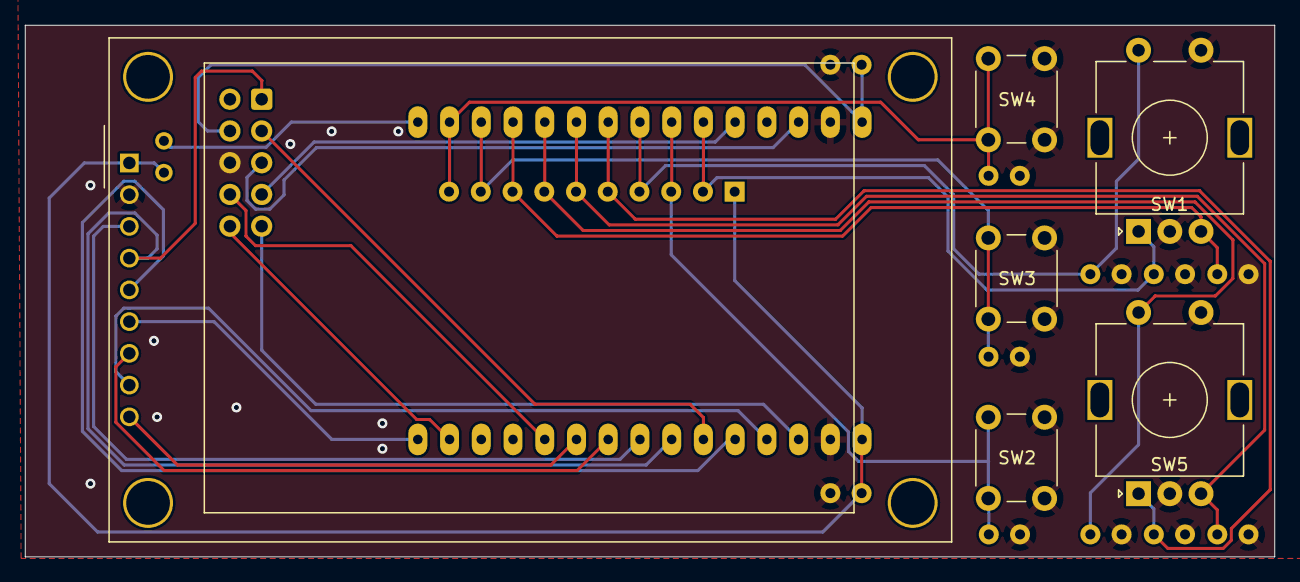
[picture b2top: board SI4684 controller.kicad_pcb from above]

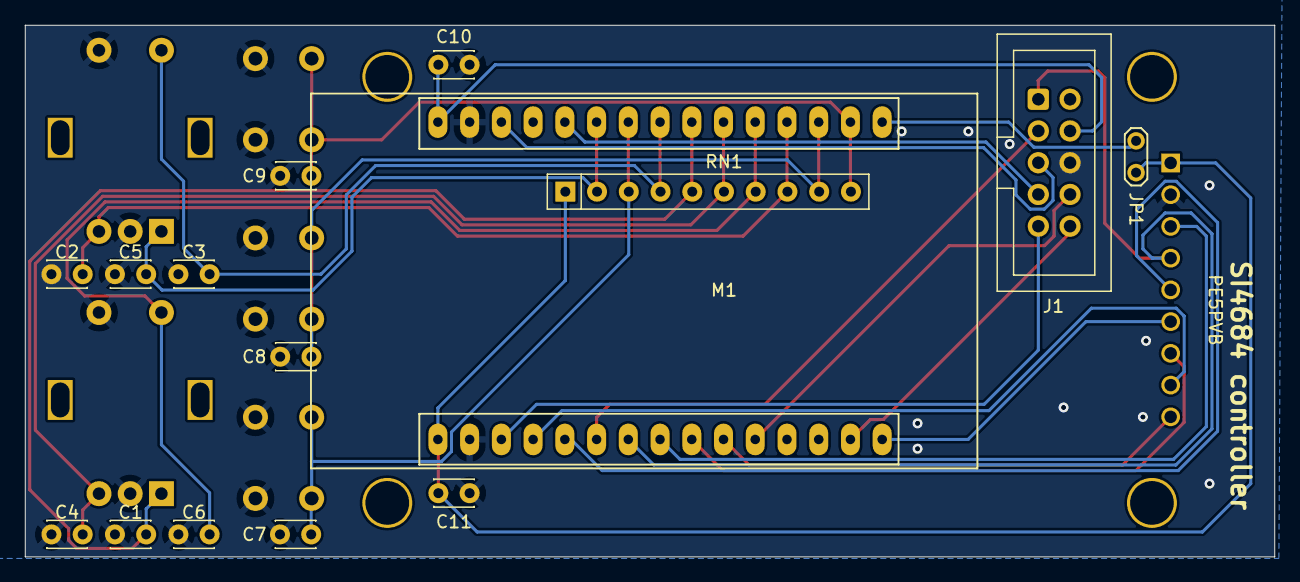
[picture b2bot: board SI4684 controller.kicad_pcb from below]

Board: 2 copper layers, 100.0 x 42.5 mm, 21 parts (15 on the bottom side), 26 nets.

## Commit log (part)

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2024-02-28 Rename
2024-02-28 Added default values
2024-02-29 progress
2024-03-11 Optimising
2024-03-11 Upload STL's
2024-03-11 Added schematics and gerbers
2024-03-11 Configure GPIOs
2024-03-11 Improvements
2024-03-12 Optimalisation
2024-03-12 Cleanup
2024-03-12 Smooth fading
2024-03-12 Bugfix in menu
2024-03-13 Some small changes and font update
2024-03-13 Frontend tuning
2024-03-13 Layout update
2024-03-13 Enabled DMA
2024-03-14 Mod on rotary encoder routine
2024-03-14 Rotary encoder mod reverted
2024-03-14 Reverted rotary mod
2024-03-14 Added some extra security for overrun due bad signal
2024-03-15 Code cleanup
2024-03-15 Update STL
2024-03-15 Moved memory channels to struct
2024-03-17 Removed double eeprom entry
2024-03-20 STL update
2024-04-29 Added German language
2024-05-12 Fixed display of NO SIGNAL, SELECT SERVICE, TUNING display in extended latin languages
2024-05-15 Fixed memory issue
2024-05-16 Fixed a problem where the radio could hang
2024-05-16 Font update
2024-05-18 Fixed a bug with EID/SID conversion
2024-05-18 Added waiting for list message when channellist is empty
2024-05-18 GUI optimalisation
2024-05-22 Update German
2024-05-23 Small update on SID/EID conversion and RDS parser (thanks Pascal)
    Added DAC volume control in API
2024-05-24 Added French
2024-06-05 Small update on PS font to fit the sprite
2024-06-12 Added charset detection
2024-07-13 Fixed a problem some muxes won't load
2024-07-20 Added serial protocol + fix error closing MOT
2024-07-21 Fixed regression in JPG viewer
2024-07-21 Added EID to Serial protocol
2024-07-22 Removed WiFi to create some free RAM
2024-07-31 Added slideshow buffering
    Auto slideshow fix.
    Bugfixes
2024-07-31 Versioning
2024-11-06 Grammar fixes
    Fixed grammar of some english words
2025-01-22 fix time and date not updating
2025-01-22 fix compilation on case sensitive systems
2025-01-26 Added Kicad files
2026-02-22 Additional bugfixing on slideshow parser
2026-02-23 Add support for IR Remote Control
2026-02-23 Forgot to add IRReceiver.h in ino file
2026-05-11 Bugfixing and remarks

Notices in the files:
README.md:
License:
This project is distributed under the **GNU General Public License v3**. See `LICENSE` for the full license text.
Contributions, bug reports and improvements are welcome through the project repository.
Those derived portions are used under the **MIT License** and retain the corresponding copyright/licence notice in the source file.
These images are **proprietary Skyworks firmware**, are not made open-source by this project, and are not covered by the GPL licence that applies to the receiver application source.
- GPL license information.
